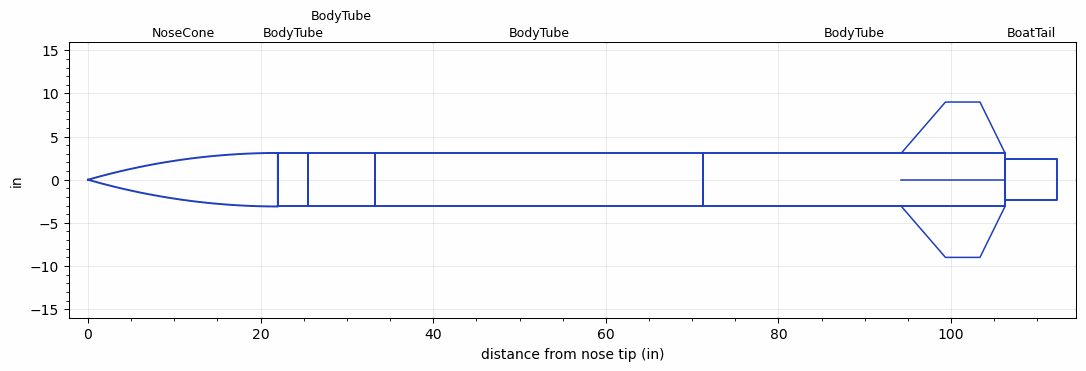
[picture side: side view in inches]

<RASAeroDocument>
 <FileVersion>2</FileVersion>
 <RocketDesign>
  <NoseCone>
   <Length>22</Length>
   <Diameter>6.2</Diameter>
   <Shape>Tangent Ogive</Shape>
   <Location>0</Location>
  </NoseCone>
  <BodyTube>
   <Length>3.5</Length>
   <Diameter>6.2</Diameter>
   <Location>22</Location>
  </BodyTube>
  <BodyTube>
   <Length>7.75</Length>
   <Diameter>6.2</Diameter>
   <Location>25.4999</Location>
  </BodyTube>
  <BodyTube>
   <Length>37.9999</Length>
   <Diameter>6.2</Diameter>
   <LaunchLugDiameter>0.3937</LaunchLugDiameter>
   <LaunchLugLength>0.5905</LaunchLugLength>
   <Location>33.2499</Location>
  </BodyTube>
  <BodyTube>
   <Length>34.9999</Length>
   <Diameter>6.2</Diameter>
   <LaunchLugDiameter>0.3937</LaunchLugDiameter>
   <LaunchLugLength>0.5905</LaunchLugLength>
   <Location>71.2499</Location>
   <Fin>
    <Count>4</Count>
    <Chord>12</Chord>
    <Span>5.9</Span>
    <SweepDistance>5.1</SweepDistance>
    <TipChord>4</TipChord>
    <Thickness>0.1875</Thickness>
    <Location>12</Location>
    <AirfoilSection>Rounded</AirfoilSection>
   </Fin>
  </BodyTube>
  <BoatTail>
   <Length>6</Length>
   <Diameter>4.75</Diameter>
   <RearDiameter>4.75</RearDiameter>
   <Location>106.2498</Location>
  </BoatTail>
  <Surface>Rough Camouflage Paint</Surface>
  <CD>0</CD>
  <ModifiedBarrowman>False</ModifiedBarrowman>
  <Turbulence>False</Turbulence>
  <UseBooster1>False</UseBooster1>
  <UseBooster2>False</UseBooster2>
 </RocketDesign>
 <LaunchSite>
  <Altitude>4595.0001</Altitude>
  <Pressure>24.9023</Pressure>
  <RodAngle>6</RodAngle>
  <RodLength>147.9997</RodLength>
  <Temperature>105</Temperature>
  <WindSpeed>10</WindSpeed>
 </LaunchSite>
 <Recovery>
  <Altitude1>1000</Altitude1>
  <Altitude2>0</Altitude2>
  <DeviceType1>Parachute</DeviceType1>
  <DeviceType2>None</DeviceType2>
  <Event1>True</Event1>
  <Event2>False</Event2>
  <Size1>143.9997</Size1>
  <Size2>0</Size2>
  <EventType1>Altitude</EventType1>
  <EventType2>None</EventType2>
  <CD1>0.97</CD1>
  <CD2>0</CD2>
 </Recovery>
 <SimulationList>
  <Simulation>
   <SustainerLaunchWt>65.3914</SustainerLaunchWt>
   <SustainerCG>67.3635</SustainerCG>
   <SustainerIgnitionDelay>0</SustainerIgnitionDelay>
   <Booster1SeparationDelay>0</Booster1SeparationDelay>
   <Booster1IgnitionDelay>0</Booster1IgnitionDelay>
   <IncludeBooster1>False</IncludeBooster1>
   <Booster2Delay>0</Booster2Delay>
   <IncludeBooster2>False</IncludeBooster2>
  </Simulation>
  <Simulation>
   <SustainerLaunchWt>65.3914</SustainerLaunchWt>
   <SustainerCG>67.3635</SustainerCG>
   <SustainerIgnitionDelay>0</SustainerIgnitionDelay>
   <Booster1SeparationDelay>0</Booster1SeparationDelay>
   <Booster1IgnitionDelay>0</Booster1IgnitionDelay>
   <IncludeBooster1>False</IncludeBooster1>
   <Booster2Delay>0</Booster2Delay>
   <IncludeBooster2>False</IncludeBooster2>
  </Simulation>
  <Simulation>
   <SustainerLaunchWt>65.3914</SustainerLaunchWt>
   <SustainerCG>67.3635</SustainerCG>
   <SustainerIgnitionDelay>0</SustainerIgnitionDelay>
   <Booster1SeparationDelay>0</Booster1SeparationDelay>
   <Booster1IgnitionDelay>0</Booster1IgnitionDelay>
   <IncludeBooster1>False</IncludeBooster1>
   <Booster2Delay>0</Booster2Delay>
   <IncludeBooster2>False</IncludeBooster2>
  </Simulation>
  <Simulation>
   <SustainerLaunchWt>65.3914</SustainerLaunchWt>
   <SustainerCG>67.3635</SustainerCG>
   <SustainerIgnitionDelay>0</SustainerIgnitionDelay>
   <Booster1SeparationDelay>0</Booster1SeparationDelay>
   <Booster1IgnitionDelay>0</Booster1IgnitionDelay>
   <IncludeBooster1>False</IncludeBooster1>
   <Booster2Delay>0</Booster2Delay>
   <IncludeBooster2>False</IncludeBooster2>
  </Simulation>
  <Simulation>
   <SustainerLaunchWt>65.3914</SustainerLaunchWt>
   <SustainerCG>67.3635</SustainerCG>
   <SustainerIgnitionDelay>0</SustainerIgnitionDelay>
   <Booster1SeparationDelay>0</Booster1SeparationDelay>
   <Booster1IgnitionDelay>0</Booster1IgnitionDelay>
   <IncludeBooster1>False</IncludeBooster1>
   <Booster2Delay>0</Booster2Delay>
   <IncludeBooster2>False</IncludeBooster2>
  </Simulation>
  <Simulation>
   <SustainerLaunchWt>65.3914</SustainerLaunchWt>
   <SustainerCG>67.3635</SustainerCG>
   <SustainerIgnitionDelay>0</SustainerIgnitionDelay>
   <Booster1SeparationDelay>0</Booster1SeparationDelay>
   <Booster1IgnitionDelay>0</Booster1IgnitionDelay>
   <IncludeBooster1>False</IncludeBooster1>
   <Booster2Delay>0</Booster2Delay>
   <IncludeBooster2>False</IncludeBooster2>
  </Simulation>
 </SimulationList>
</RASAeroDocument>
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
